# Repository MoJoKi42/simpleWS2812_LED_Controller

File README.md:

# simpleWS2812_LED_Controller
WS2812 LED Controller with AVR µC and 5V Buck-Converter

<ins>Software/µC:</ins>
- **ATMega328P-AU**
- 8 different color effects
- see "AVR_Code" for code and fuse setting

<ins>Hardware:</ins>
- 12V Input
- 5V Output
- max. 5m strip length

finished Board and construction with case:

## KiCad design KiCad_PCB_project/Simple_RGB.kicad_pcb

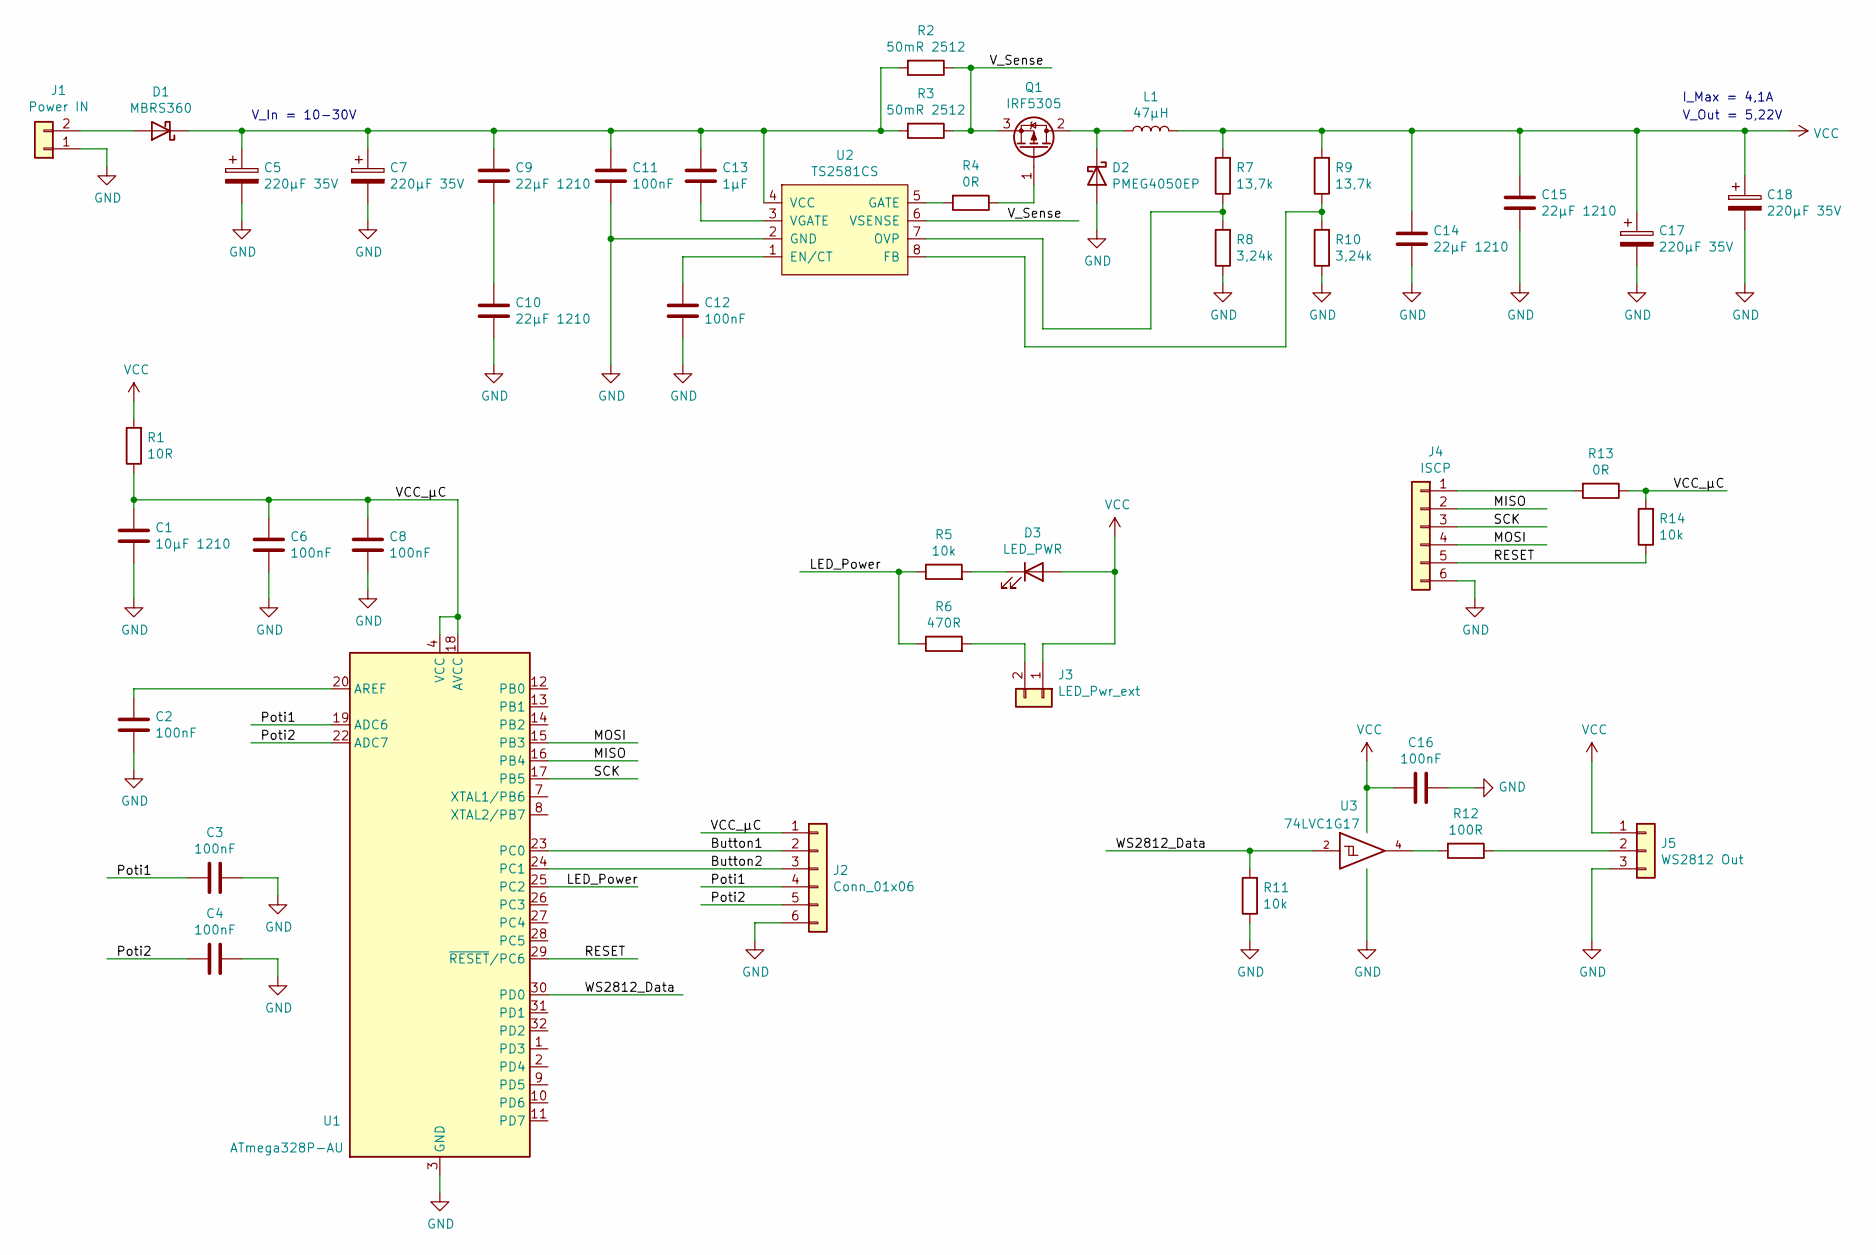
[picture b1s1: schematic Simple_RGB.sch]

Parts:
C1: 10µF 1210; C_1210_3225Metric_Pad1.33x2.70mm_HandSolder
C2, C3, C4, C6, C8, C11, C12, C16: 100nF; C_0805_2012Metric_Pad1.18x1.45mm_HandSolder
C5, C7, C17, C18: 220µF 35V; CP_Radial_D10.0mm_P5.00mm
C9, C10, C14, C15: 22µF 1210; C_1210_3225Metric_Pad1.33x2.70mm_HandSolder
C13: 1µF; C_0805_2012Metric_Pad1.18x1.45mm_HandSolder
D1: MBRS360; D_SMC_Handsoldering
D2: PMEG4050EP; D_SOD-128
D3: LED_PWR; LED_PLCC-2
J1: Power IN; TerminalBlock_RND_205-00001_1x02_P5.00mm_Horizontal
J2: Conn_01x06; JST_XH_B6B-XH-A_1x06_P2.50mm_Vertical
J3: LED_Pwr_ext; JST_XH_B2B-XH-A_1x02_P2.50mm_Vertical
J4: ISCP; PinHeader_1x06_P2.54mm_Vertical
J5: WS2812 Out; TerminalBlock_RND_205-00002_1x03_P5.00mm_Horizontal
L1: 47µH; L_Fastron_PISR_Handsoldering
Q1: IRF5305; TO-220-3_Vertical
R1: 10R; R_0805_2012Metric_Pad1.20x1.40mm_HandSolder
R2, R3: 50mR 2512; R_2512_6332Metric_Pad1.40x3.35mm_HandSolder
R4, R13: 0R; R_0805_2012Metric_Pad1.20x1.40mm_HandSolder
R5, R11, R14: 10k; R_0805_2012Metric_Pad1.20x1.40mm_HandSolder
R6: 470R; R_0805_2012Metric_Pad1.20x1.40mm_HandSolder
R7, R9: 13,7k; R_0805_2012Metric_Pad1.20x1.40mm_HandSolder
R8, R10: 3,24k; R_0805_2012Metric_Pad1.20x1.40mm_HandSolder
R12: 100R; R_0805_2012Metric_Pad1.20x1.40mm_HandSolder
U1: ATmega328P-AU; TQFP-32_7x7mm_P0.8mm
U2: TS2581CS; SOP-8_3.9x4.9mm_P1.27mm
U3: 74LVC1G17; SOT-23-5_HandSoldering

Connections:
/Button1: J2.2, U1.23 (PC0)
/Button2: J2.3, U1.24 (PC1)
/LED_Power: R5.1, R6.1, U1.25 (PC2)
/MISO: J4.2, U1.16 (PB4)
/MOSI: J4.4, U1.15 (PB3)
/Poti1: C3.2, J2.4, U1.19 (ADC6)
/Poti2: C4.2, J2.5, U1.22 (ADC7)
/RESET: J4.5, R14.1, U1.29 (~RESET~/PC6)
/SCK: J4.3, U1.17 (PB5)
/VCC_µC: C1.1, C6.1, C8.1, J2.1, R1.1, R13.1, R14.2, U1.4 (VCC), U1.6 (VCC), U1.18 (AVCC)
/V_Sense: Q1.3 (S), R2.1, R3.1, U2.6 (VSENSE)
/WS2812_Data: R11.2, U1.30 (PD0), U3.2
GND: C1.2, C2.2, C3.1, C4.1, C5.2, C6.2, C7.2, C8.2, C10.2, C11.2, C12.2, C14.2, C15.2, C16.1, C17.2, C18.2, D2.2 (A), J1.1, J2.6, J4.6, J5.3, R8.1, R10.1, R11.1, U1.3 (GND), U1.5 (GND), U1.21 (GND), U2.2 (GND), U3.3 (GND)
unnamed: C2.1, U1.20 (AREF)
unnamed: C9.2, C10.1
unnamed: C5.1, C7.1, C9.1, C11.1, C13.1, D1.1 (K), R2.2, R3.2, U2.4 (VCC)
unnamed: C12.1, U2.1 (EN/CT)
unnamed: C13.2, U2.3 (VGATE)
unnamed: D1.2 (A), J1.2
unnamed: D2.1 (K), L1.1, Q1.2 (D)
unnamed: D3.1 (K), R5.2
unnamed: J3.2, R6.2
unnamed: J4.1, R13.2
unnamed: J5.2, R12.1
unnamed: Q1.1 (G), R4.1
unnamed: R4.2, U2.5 (GATE)
unnamed: R7.1, R8.2, U2.7 (OVP)
unnamed: R9.1, R10.2, U2.8 (FB)
unnamed: R12.2, U3.4
VCC: C14.1, C15.1, C16.2, C17.1, C18.1, D3.2 (A), J3.1, J5.1, L1.2, R1.2, R7.2, R9.2, U3.5 (VCC)

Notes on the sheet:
V_Out = 5,22V
V_In = 10-30V
I_Max = 4,1A

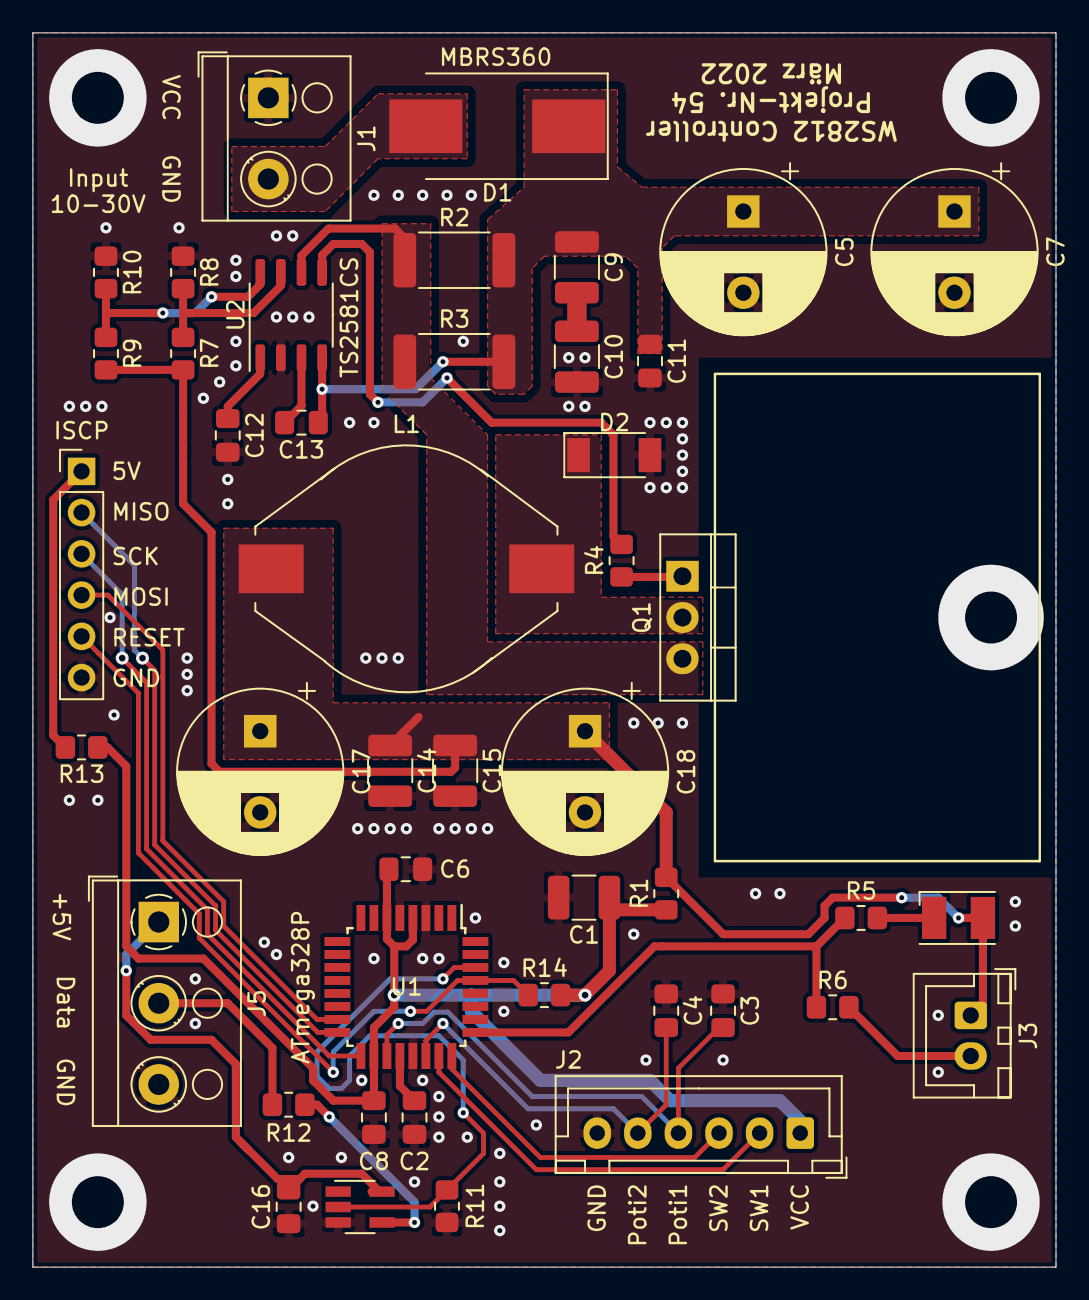
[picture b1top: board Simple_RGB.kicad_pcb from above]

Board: 2 copper layers, 63.0 x 76.0 mm, 45 parts (0 on the bottom side), 30 nets.

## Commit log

2023-03-30 init
2023-03-30 removed README
